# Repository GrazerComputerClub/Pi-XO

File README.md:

# Pi-XO
Raspberry Pi Zero game console for use with PICO-8.   
Development discontinued  

If you are interested in a PCB board or components, please contact us via our email.

## In Action

## Errata

Rev. 01. board  error:
  - **Error:** Speaker- an audio amp. output- connected to GND.  
    **Solution:** Do not wire speaker and audio amp. output (PAD5 and PAD6) to PCB, please connect speaker to audio amp. output via wire.  
    **Drawback:** Headphone connector not working 
  - **Error:**  ADC input direct connected to batterie A result in applying ~0.6 V to 3.3 V supply if battery is attached and device is off.  
    **Solution:** Do not assemble MCP3202 (IC1).  
    **Drawback:** No battery monitoring possible.
  - **Error:**  Dual NiMH AA-Batteries in combination with DD0606SA_3V7 - DC/DC Step Up Converter cannot provide enough current for Wi-Fi operation (consumes up to 250 mA).  
    **Solution 1:** Use Raspberry Pi Zero v1.3 or switch off Wi-Fi at Raspberry Pi Zero W/WH.  
    **Drawback:** Download of games only via Eternet OTG Mode possible or manual copy to sd card  
    **Solution 2:** Use 4xAAA NiMH battery without DC/DC Step Up Converter 
    
## Features

- **Multiple display options** - 160x128 or 320x240   
- **Audio (speaker / headphone)**
- **Classic NiMH battery supply**
- **Battery monitoring**
- **GPIOs (LED bar)**
- **Vibration motors**
- **Low cost**

## OS installation

- Download latest Raspjamming-Image https://github.com/GrazerComputerClub/Raspjamming-Image and flash to SD card
- Unzip PICO-8-rasp.zip (https://www.lexaloffle.com/pico-8.php) to boot partition (Executable needed pico-8/pico8) from 
- Activate line 'include Pi-XO.txt' in config.txt file
- Activate correct Display Option 1-3 including resolution in Pi-XO.txt file 
   * Display 1: 320x240 Display mounted far right side (9 pin, BK-LED regulation)
   * Display 2: 160x128 Display mounted right side (8 pin, BK-LED regulation) 
   * Display 3: 160x128 Display mounted left side  (11 pin, BK-LED fixed on) 

## Functions button

- Fn-Button and Up/Down-Button: Volume control
- Fn-Button and Left/Right-Button: Display brightness (Display 1 and 2)
- Fn-Button and P-Button: Shutdown

## Diagrams and pictures

## Assembling

### Components list
	
 1 x Female pin header socket 2x20  (JP1)
 1 x Switch 3-pin (S9, Device on/off)  
 1 x 2Pin + Jumper or Switch 2-pin (JP6, vibration motors on/off)    
 8 x Tactile switch 6x6mm (S1-S8)  
     https://www.reichelt.com/at/en/short-stroke-key-6x6-mm-height-5-0-mm-12-v-vertical-taster-9302-p44579.html  
 1 x Audio amplifier board PAM8302 (JP3, do not connect PAD5 and PAD6)  
     https://www.ebay.de/sch/i.html?_nkw=PAM8302  
 1 x DD0606SA_3V7 - DC/DC Step Up Converter to 3.7V (JP2)  
     https://www.google.com/search?q=DD0606SA_3V7  
 1 x Speaker 8 Ohm (connect to amplifier board PAM8302 Output via wire, SP1)  
     https://www.reichelt.com/at/en/metal-speaker-soldered-connection-lsm-36m-b-p145887.html  
     https://www.neuhold-elektronik.at/catshop/product_info.php?products_id=6645  
 1 x LED bar 8 segments (LB10, align right site)  
     https://www.ebay.at/sch/i.html?_from=R40&_trksid=m570.l1313&_nkw=8-Segment+Red+Color+Bar  
 1 x Resistor array 1K (RN1)  
     https://secure.reichelt.at/resistor-network-8-res-9-pin-1-0-k-x2126-sil-9-8-1-0k-p18012.html  
 2 x Vibration motor (JP4, JP5)  
     https://www.neuhold-elektronik.at/catshop/product_info.php?products_id=6971  
 2 x AA Batterie holder (needs DC/DC Step Up Converter) or dual AAA Batteries holder (no DC/DC Step Up Converter needed) (PAD1, PAD2, PAD3, PAD4)  
     https://secure.reichelt.at/battery-holder-1x-mignon-aa-halter-1xaap-p113168.html  
     https://secure.reichelt.at/holder-for-1-mignon-cell-aa-solder-tag-halter-1xum3-lf-p8434.html  
     https://secure.reichelt.at/battery-holder-2x-mignon-aa-halter-2xaaz-p113169.html  
 2 x BC547B transiior (T1, T2)  
     https://secure.reichelt.at/npn-to-92-transistor-45-v-0-1-a-0-5-w-bc-547b-p5006.html  
 1 x BC557B transistor (Q2)  
     https://secure.reichelt.at/transistor-pnp-to-92-45-v-0-1-a-0-5-w-bc-557b-p35845.html  
 2 x Resistor 2K2 Ohm (Transistor base vibration motor: R1, R2)  
 1 x Resistor 270 Ohm (Audio filter: R3)  
 1 x Resistor 150 Ohm (Audio filter: R4)  
 3 x Resistor 1K Ohm (protection UART: R5, R6; transistor background LED display: R7)   
 1 x Capacitor 33 nF (C1)  
 1 x Electrolytic capacitor 10 uF/6.3 V (C2)  
 1 x Capacitor 100 nF (C5)  
 1 x Electrolytic capacitor 330 uF/6.3 V (C6)  
 1 x MCP3202 (IC1, do not connect)  
     https://www.conrad.at/de/p/microchip-technology-mcp3202-ci-p-datenerfassungs-ic-analog-digital-wandler-adc-extern-pdip-8-651461.html  
 1 x Headphone connector (X2, do not connect)  
     https://secure.reichelt.at/jack-socket-3-5-mm-pcb-with-switch-contact-ebs-35-p7301.htm  
 2 x Diode 1N4001 (D2 or D4, D1 or D3)  
     https://secure.reichelt.at/rectifier-diode-do41-50-v-1-a-1n-4001-p1723.html  
 1 x 1,8" Display 160x128 ST7735 11-pin (JP7) or 8-pin (JP11) - https://www.ebay.de/sch/i.html?_nkw=1.8+128x160+ST7735  
     2,2" Display 320x240 ILI9341 9-pin (JB8) - https://www.ebay.de/sch/i.html?_nkw=2.2+ILI9341+240x320

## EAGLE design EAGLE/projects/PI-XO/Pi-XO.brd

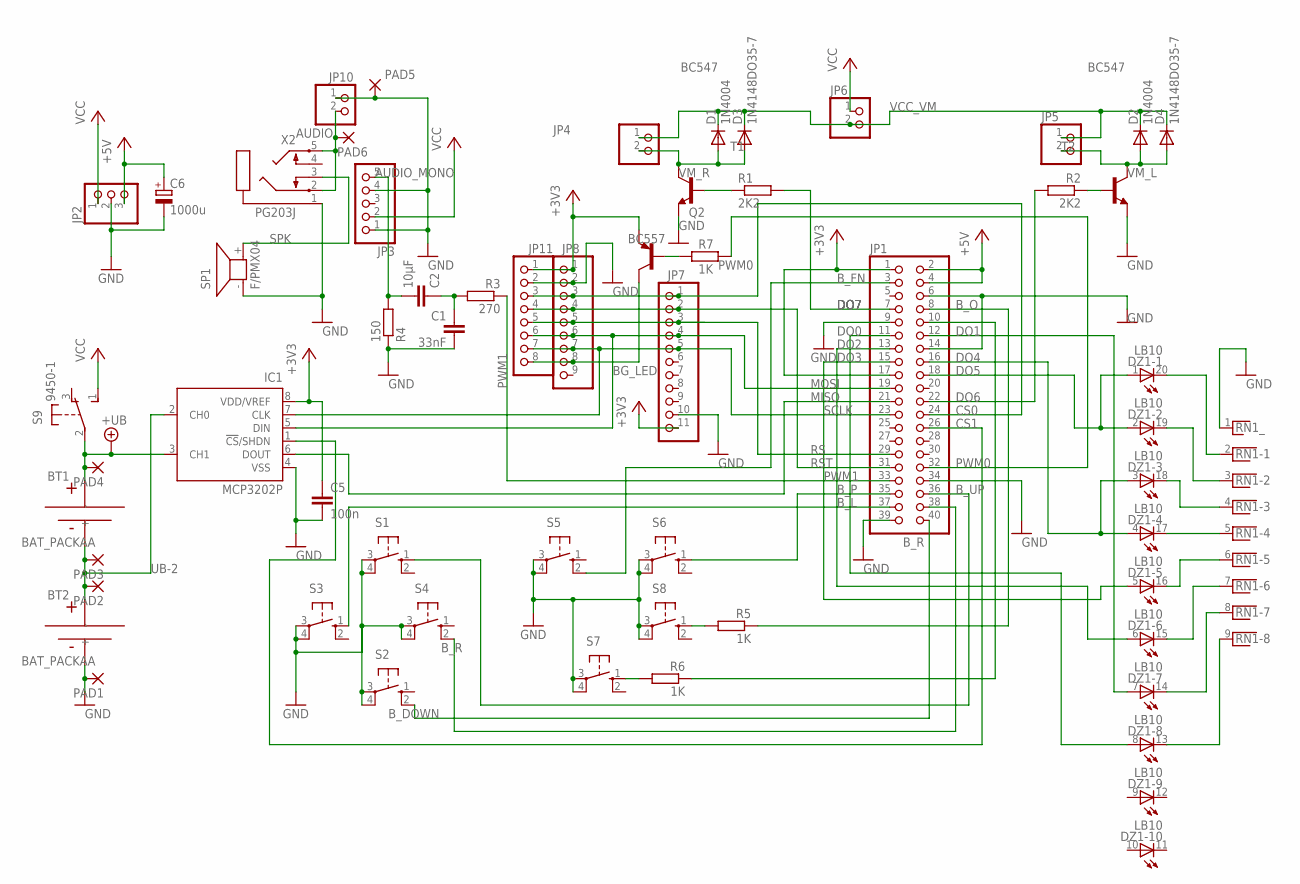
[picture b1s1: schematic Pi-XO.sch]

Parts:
BT1, BT2: BAT_PACKAA; BHAA-3
C1: 33nF; C050-024X044
C2: 10µF; C050-024X044
C5: 100n; C025-030X050
C6: 1000u; B45181A
D1, D2: 1N4004; DO41-10
D3, D4: 1N4148DO35-7; DO35-7
DZ1: LB10
IC1: MCP3202P; DIL8
JP1: PINHD-2X20; 2X20
JP2: PINHD-1X3; 1X03
JP3: PINHD-1X5; 1X05
JP4, JP5, JP6, JP10: PINHD-1X2; 1X02
JP7: PINHD-1X11; 1X11
JP8: PINHD-1X9; 1X09
JP11: PINHD-1X8; 1X08
PAD1, PAD2, PAD3, PAD4: 3,81/1,4
PAD5, PAD6: 2,15/1,0
Q2: BC557; TO92
R1, R2: 2K2; 0204/7
R3: 270; 0204/7
R4: 150; 0204/7
R5, R6, R7: 1K; 0204/7
RN1: RNX8; RN-9
S1, S2, S3, S4, S5, S6, S7, S8: 10-XX; B3F-10XX
S9: 9450-1
SP1: F/PMX04; F/PMX04A
T1, T2: BC547; TO92
X2: PG203J

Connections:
+3V3: C5.1, IC1.8 (VDD/VREF), JP1.1, JP1.17, JP7.11, JP8.1, JP11.1, Q2.1 (E)
+5V: C6.+, JP1.2, JP1.4, JP2.3
+UB: BT1.+, IC1.3 (CH1), PAD4.1, S9.2
AUDIO: JP10.2, PAD6.1, X2.2, X2.5
AUDIO_MONO: C2.2, JP3.5, R4.2
BG_LED: JP8.8, JP11.8, Q2.3 (C)
B_DOWN: JP1.40, S2.2 (S1)
B_FN: JP1.3, S5.2 (S1)
B_L: JP1.37, S3.1 (S)
B_O: JP1.8, R5.1
B_P: JP1.35, S6.1 (S)
B_R: JP1.38, S4.2 (S1)
B_UP: JP1.36, S1.1 (S)
B_X: JP1.10, R6.1
CS0: JP1.24, JP7.1, JP8.3, JP11.3
CS1: IC1.1 (!CS!/SHDN), JP1.26
DO0: DZ1.8 (A), JP1.11
DO1: DZ1.7 (A), JP1.12
DO2: DZ1.6 (A), JP1.13
DO3: DZ1.5 (A), JP1.15
DO4: DZ1.3 (A), DZ1.4 (A), JP1.16
DO5: DZ1.1 (A), DZ1.2 (A), JP1.18
DO6: JP1.22, R2.2
DO7: JP1.7, R1.2
GND: BT2.-, C1.2, C5.2, C6.-, IC1.4 (VSS), JP1.6, JP1.9, JP1.14, JP1.34, JP1.39, JP2.2, JP3.1, JP3.4, JP7.10, JP8.2, JP10.1, JP11.2, PAD1.1, PAD5.1, R4.1, RN1.1, S1.3, S1.4 (P1), S2.3, S2.4 (P1), S3.3, S3.4 (P1), S4.3, S4.4 (P1), S5.3, S5.4 (P1), S6.3, S6.4 (P1), S7.3, S7.4 (P1), S8.3, S8.4 (P1), SP1.- (1), T1.1 (E), T2.1 (E), X2.1
MISO: IC1.6 (DOUT), JP1.21
MOSI: IC1.5 (DIN), JP1.19, JP7.4, JP8.6, JP11.6
unnamed: C1.1, C2.1, R3.2
unnamed: R1.1, T1.2 (B)
unnamed: R2.1, T2.2 (B)
unnamed: DZ1.20 (C), RN1.2
unnamed: DZ1.19 (C), RN1.3
unnamed: DZ1.18 (C), RN1.4
unnamed: DZ1.17 (C), RN1.5
unnamed: DZ1.16 (C), RN1.6
unnamed: DZ1.15 (C), RN1.7
unnamed: DZ1.14 (C), RN1.8
unnamed: DZ1.13 (C), RN1.9
unnamed: R5.2, S8.1 (S)
unnamed: R6.2, S7.1 (S)
unnamed: Q2.2 (B), R7.1
PWM0: JP1.32, R7.2
PWM1: JP1.33, R3.1
RS: JP1.29, JP7.3, JP8.5, JP11.5
RST: JP1.31, JP7.2, JP8.4, JP11.4
SCLK: IC1.7 (CLK), JP1.23, JP7.5, JP8.7, JP11.7
SPK: SP1.+ (2), X2.3
UB-2: BT1.-, BT2.+, IC1.2 (CH0), PAD2.1, PAD3.1
VCC: JP2.1, JP3.2, JP6.1, S9.1 (S)
VCC_VM: D1.C, D2.C, D3.C, D4.C, JP4.1, JP5.1, JP6.2
VM_L: D2.A, D4.A, JP5.2, T2.3 (C)
VM_R: D1.A, D3.A, JP4.2, T1.3 (C)

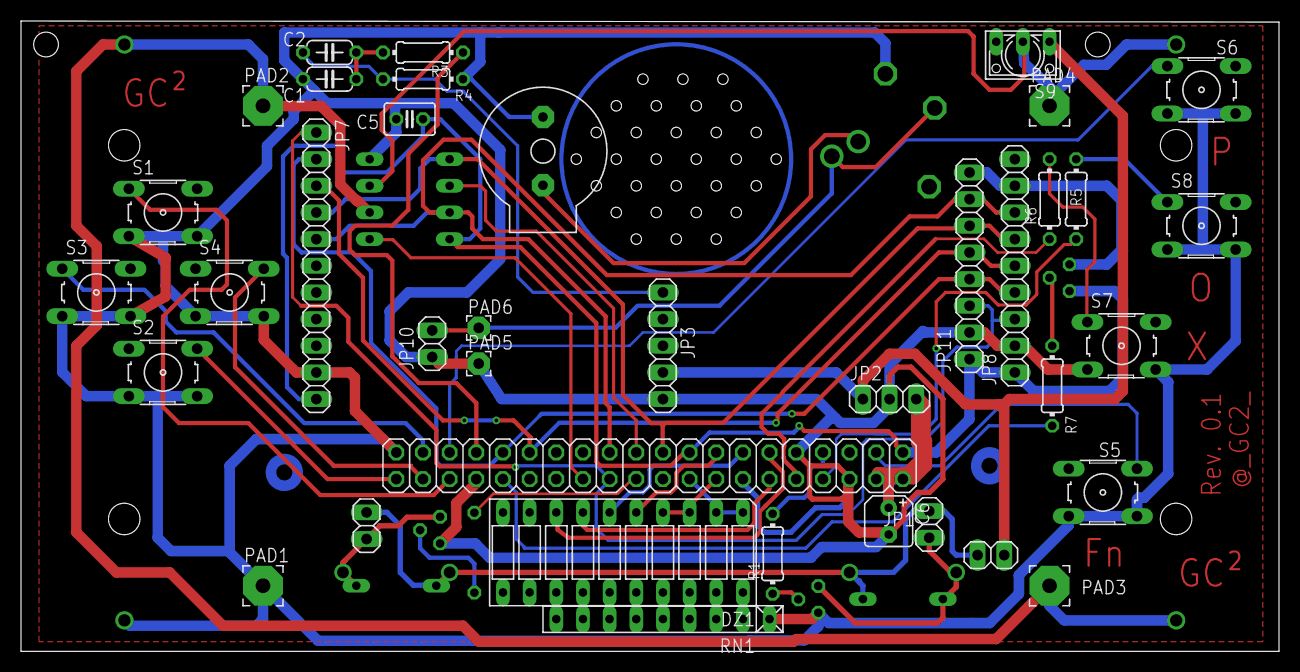
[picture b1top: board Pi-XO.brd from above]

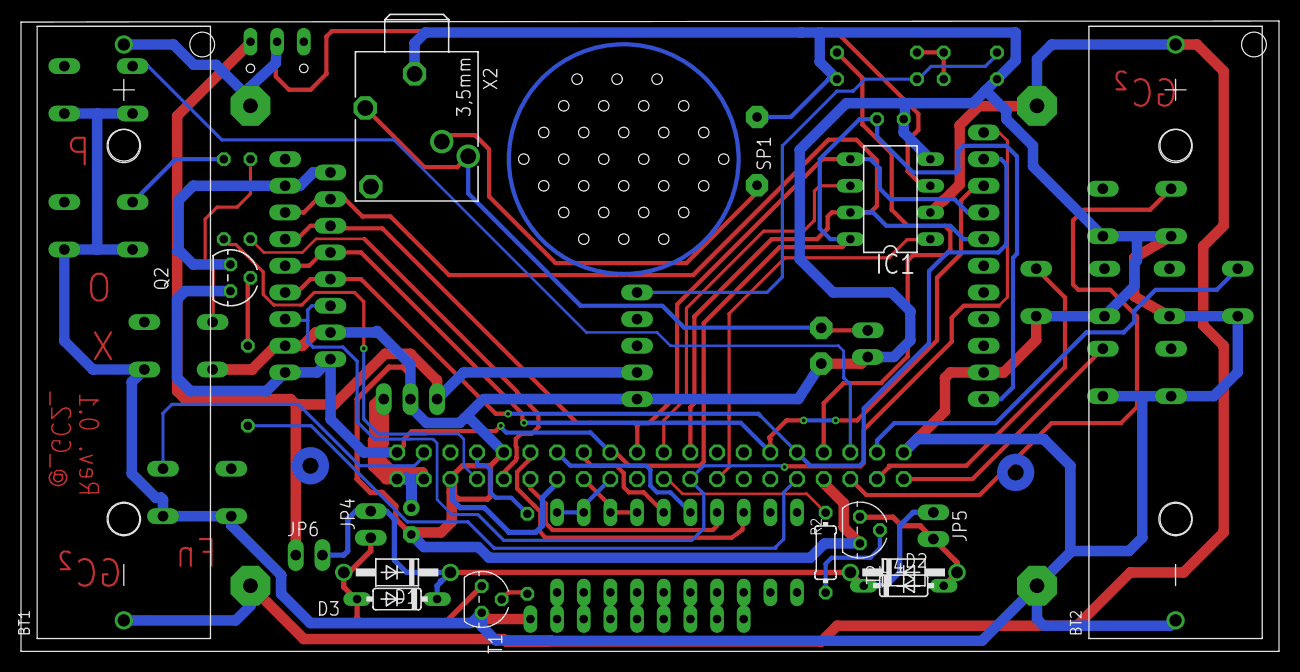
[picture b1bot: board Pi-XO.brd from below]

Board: 2 copper layers, 119.8 x 60.0 mm, 50 parts (12 on the bottom side), 52 nets.

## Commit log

2019-04-19 initial website
2019-04-20 Create CNAME
2019-04-24 Create Pi-XO
